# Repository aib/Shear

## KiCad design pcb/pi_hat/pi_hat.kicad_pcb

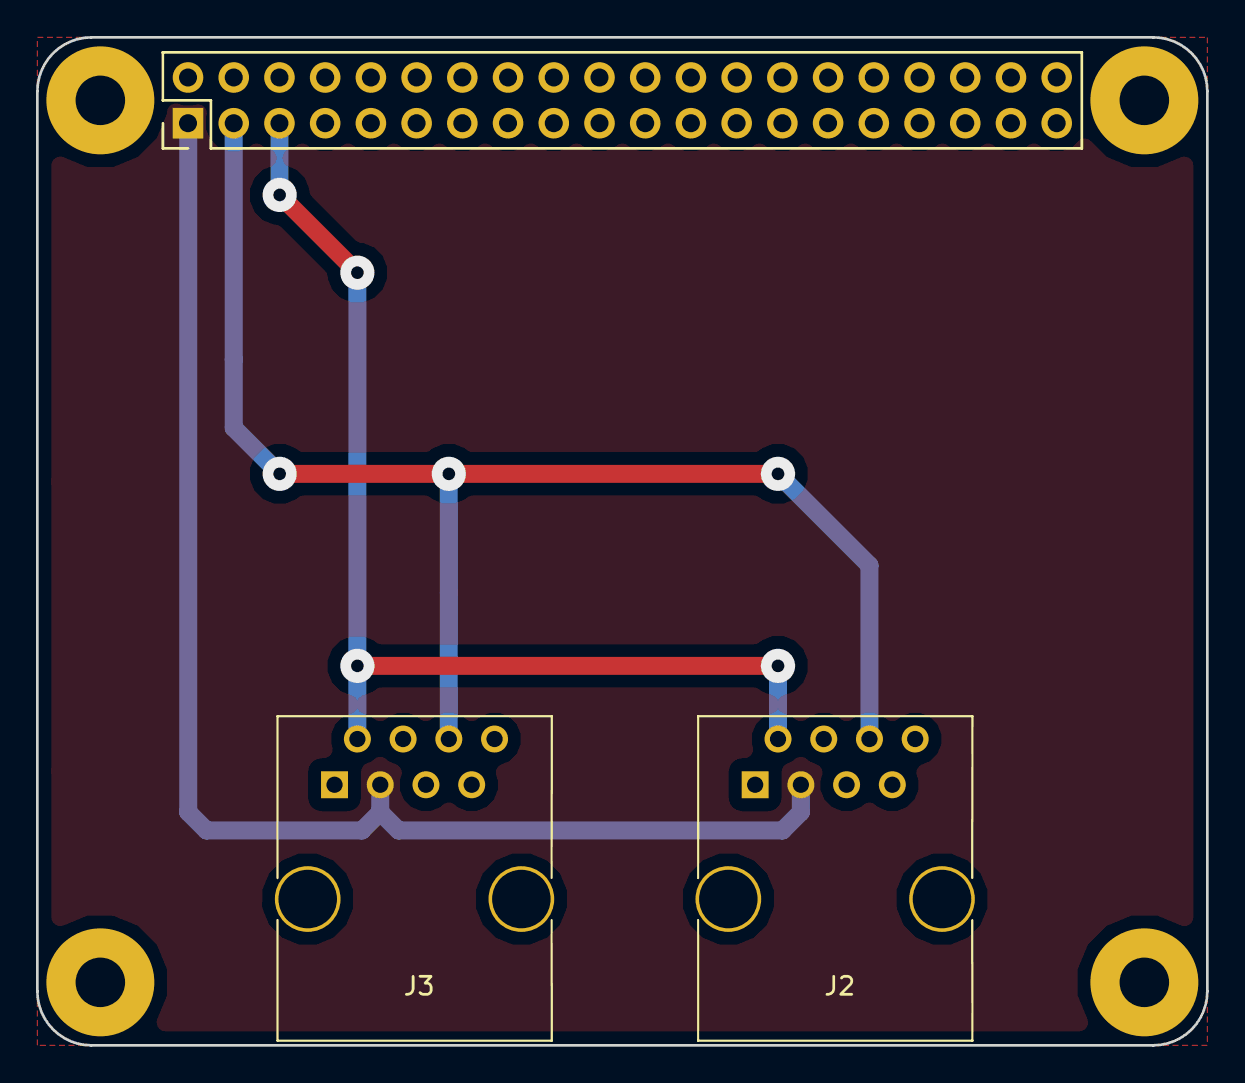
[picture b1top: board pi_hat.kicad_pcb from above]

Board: 2 copper layers, 65.0 x 56.0 mm, 3 parts (0 on the bottom side), 4 nets.

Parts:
J1: Conn_02x20_Odd_Even; RaspberryPi_3_ModelB
J2, J3: RJ45; RJ45_8

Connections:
/SCL: J1.5, J2.2, J3.2
/SDA: J1.3, J2.6, J3.6
GND: J1.9, J2.1, J3.1
VCC: J1.1, J2.3, J3.3

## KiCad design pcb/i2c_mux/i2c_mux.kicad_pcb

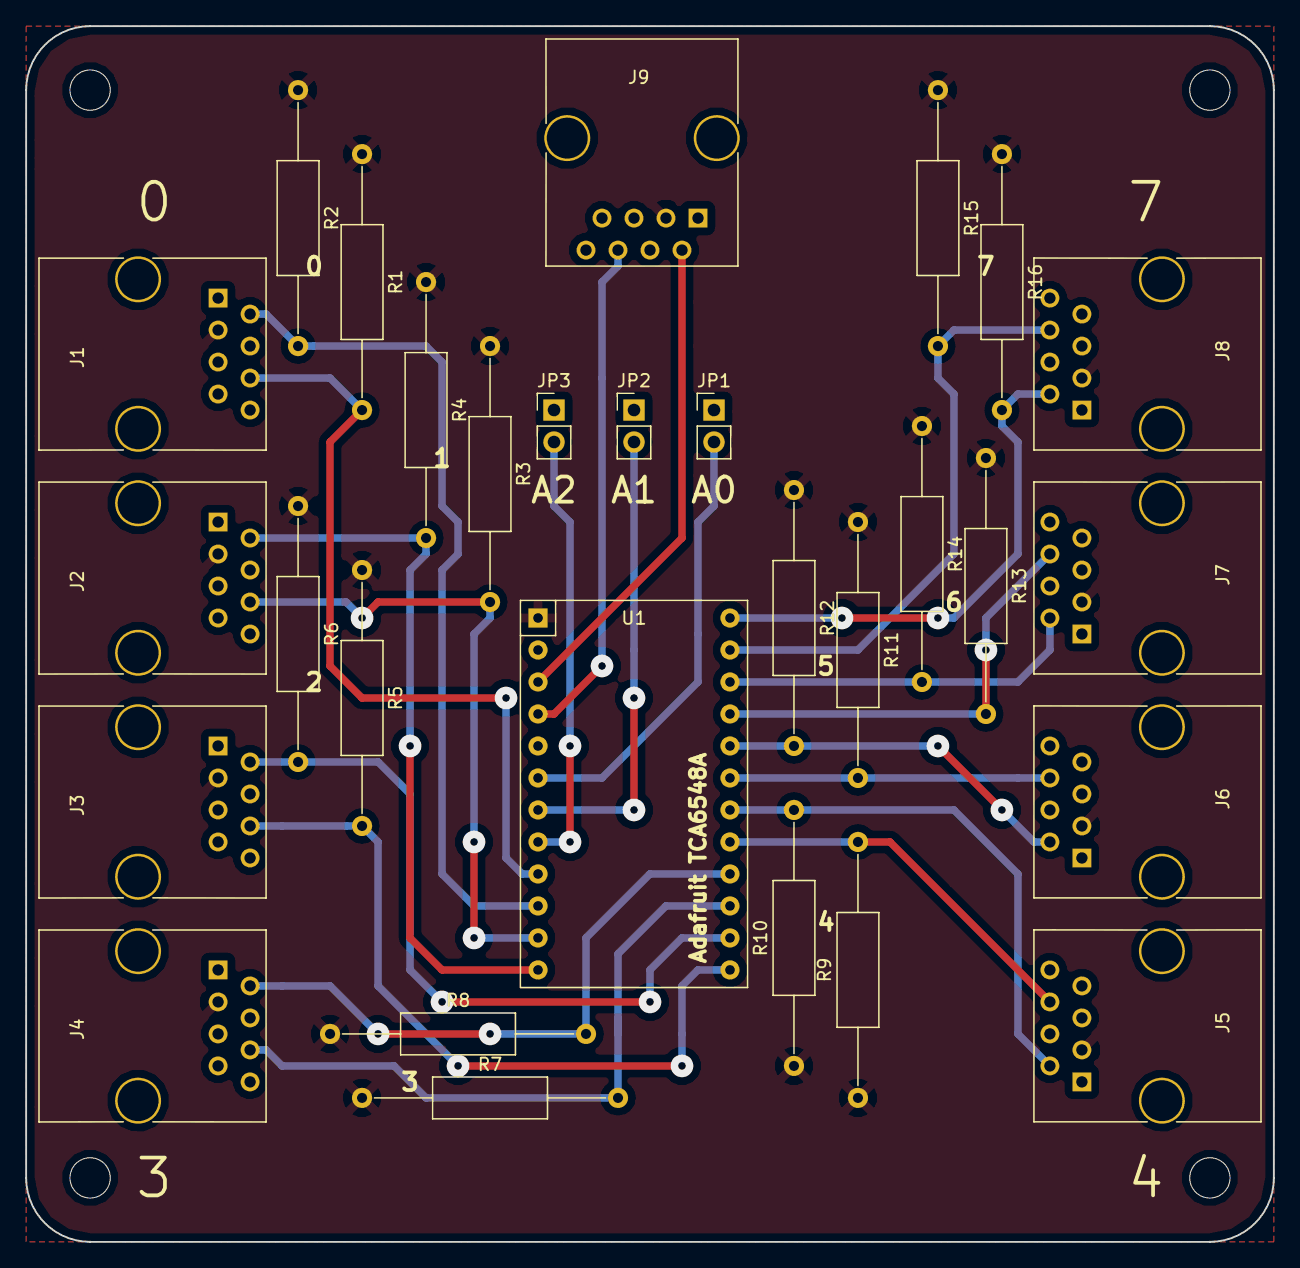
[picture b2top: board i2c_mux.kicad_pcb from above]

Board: 2 copper layers, 99.1 x 96.5 mm, 29 parts (0 on the bottom side), 23 nets.

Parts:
J1, J2, J3, J4, J5, J6, J7, J8, J9: RJ45; RJ45_8
JP1, JP2, JP3: Jumper_NO_Small; Pin_Header_Straight_1x02_Pitch2.54mm
R1, R2, R3, R4, R5, R6, R7, R8, R9, R10, R11, R12, R13, R14, R15, R16: R_Small; R_Axial_DIN0309_L9.0mm_D3.2mm_P20.32mm_Horizontal
U1: Adafruit_TCA6548A; Adafruit_TCA9548A

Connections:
GND: J1.1, J2.1, J3.1, J4.1, J5.1, J6.1, J7.1, J8.1, J9.1, JP1.1, JP2.1, JP3.1, U1.2
unnamed: J1.2, R2.2, U1.10
unnamed: J1.6, R1.2, U1.9
unnamed: J2.2, R4.2, U1.12
unnamed: J2.6, R3.2, U1.11
unnamed: J3.2, R6.2, U1.14
unnamed: J3.6, R5.2, U1.13
unnamed: J4.2, R8.2, U1.16
unnamed: J4.6, R7.2, U1.15
unnamed: J5.2, R10.2, U1.18
unnamed: J5.6, R9.2, U1.17
unnamed: J6.2, R12.2, U1.20
unnamed: J6.6, R11.2, U1.19
unnamed: J7.2, R14.2, U1.22
unnamed: J7.6, R13.2, U1.21
unnamed: J8.2, R16.2, U1.24
unnamed: J8.6, R15.2, U1.23
unnamed: J9.2, U1.3
unnamed: J9.6, U1.4
unnamed: JP1.2, U1.6
unnamed: JP2.2, U1.7
unnamed: JP3.2, U1.8
VCC: J1.3, J2.3, J3.3, J4.3, J5.3, J6.3, J7.3, J8.3, J9.3, R1.1, R2.1, R3.1, R4.1, R5.1, R6.1, R7.1, R8.1, R9.1, R10.1, R11.1, R12.1, R13.1, R14.1, R15.1, R16.1, U1.1

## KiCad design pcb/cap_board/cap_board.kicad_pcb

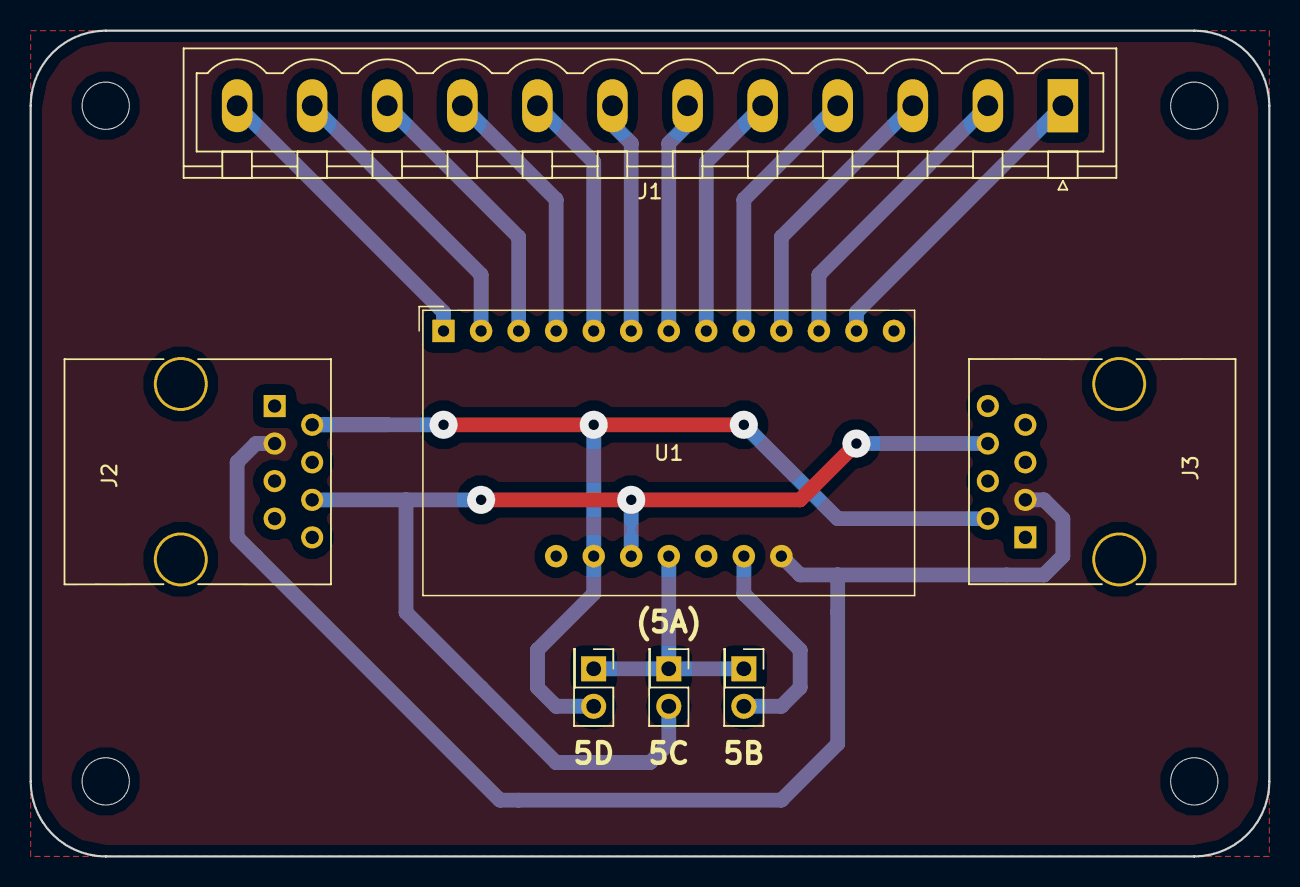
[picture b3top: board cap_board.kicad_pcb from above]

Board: 2 copper layers, 83.8 x 55.9 mm, 7 parts (0 on the bottom side), 18 nets.

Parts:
J1: Conn_01x12; PhoenixContact_MSTBVA-G_12x5.08mm_Vertical
J2, J3: RJ45; RJ45_8
JP1, JP2, JP3: Jumper_NO_Small; Pin_Header_Straight_2x01_Pitch2.54mm
U1: Adafruit_MPR121

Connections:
/SCL: J2.2, J3.2, JP3.2, U1.2
/SDA: J2.6, J3.6, JP2.2, U1.3
GND: J2.1, J3.1, U1.5, U1.8
unnamed: J1.1, U1.9
unnamed: J1.2, U1.10
unnamed: J1.3, U1.11
unnamed: J1.4, U1.12
unnamed: J1.5, U1.13
unnamed: J1.6, U1.14
unnamed: J1.7, U1.15
unnamed: J1.8, U1.16
unnamed: J1.9, U1.17
unnamed: J1.10, U1.18
unnamed: J1.11, U1.19
unnamed: J1.12, U1.20
unnamed: JP1.1, JP2.1, JP3.1, U1.4
unnamed: JP1.2, U1.6
VCC: J2.3, J3.3, U1.7

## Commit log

2016-09-20 Add link to Raspbian distribution
2016-09-20 Add ansible config with sensible defaults
2016-09-20 Add tool for detecting MPR121's on the I2C bus
2016-09-20 Add Ansible script setting up the Pi
    ...with only I2C stuff for now
2016-09-20 Use rsync to copy project directory to Pi
2016-09-20 Import Adafruit's MPR121 library
2016-09-20 Import Adafruit's GPIO library
2016-09-20 Ignore Python cache files
2018-11-19 Add 'sudo' to an external command requiring root
2018-11-19 Install Python 3 and pip
2018-11-19 Group apt installs
2018-11-19 Change MPR121 settings to match those of Bare Conductive
2018-11-19 Ignore /misc/
2018-11-19 Add fluidsynth, a SF2 and audio libraries
2018-11-19 Install Adafruit's PureIO library
2018-11-19 Remove pi-bluetooth and ntp
2018-11-19 Add script for testing the modules
2018-11-19 Remove packages no longer needed
2018-11-19 Disable some unnecessary boot scripts
2018-11-19 Add midi.py written earlier
2018-11-19 Add prototype instrument program
    with MIDI output and key mapping
2018-11-19 Add error handling; shields can now be hot plugged
2018-11-19 Enable all shields
2018-11-19 Add runner script for Fluidsynth
2018-11-19 Mount filesystems read-only
2018-11-19 Send all notes off on Ctrl-C
2018-11-19 Use insserv instead of the service module to disable services
    Do not disable console-setup
2018-11-19 Remove instrument.py
2018-11-19 Do not install i2c-tools twice!
2018-11-19 Remove unnecessary packages, use busybox syslogd instead of rsyslog
2018-11-19 Rename "become"s to "sudo"s; deprecation be damned!
2018-11-19 Run synth and keyboard at boot
2018-11-19 Increase DHCP lease time to 4h
2018-11-19 Set fluidsynth gain
2018-11-19 Install python-rtmidi
2018-11-19 Load SF2 in cfg file and set channels
2018-11-19 Start tuning the instrument
2018-11-19 Change to a dual-setup midi.py
2018-11-19 Filter *.pyc while copying
2018-11-19 Add scripts for setting up an ethernet connection with the Pi
2018-11-19 Do not use a lease file for the DHCP server
2018-11-19 Change kernel parameters
2018-11-19 Set sound output and value
2018-11-19 Rename runfluid.sh to run.sh
2018-11-19 Print MIDI notes (and channel) along with key numbers
2018-11-19 Add the MPR121 breakout footprint
2018-11-19 Add ansible inventory file
2018-11-19 Disable keyboard-setup and console-setup
2018-11-19 Add the MPR121 breakout schematic component
2018-11-19 Add the Pi hat project
2018-11-19 Add the TT setup
2018-11-19 Remove 'misc' directory, most of the stuff is already in my dotfiles
2018-11-19 Revert "Add the TT setup"
    This reverts commit 7f819ac6f6b5824fb270671cab77ea756a12f661.
2018-11-19 Add private key file since ansible now seems to accept relative paths
2018-11-19 Add the initial PCB design
2018-11-19 Add front plate zone
2018-11-19 Change screw terminals to 5.08mm pitch and add RJ45 footprints
2018-11-19 Add mounting holes and round the board
2018-11-19 Revert "Change to a dual-setup midi.py"
    This reverts commit 23491e4e4b4dfb68b9938927f0bcc5239a5617bc.
2018-11-19 Add the sensor board project
2018-11-19 Trade the long ground loop for a 5th jumper :/
2018-11-19 Change +5V to VCC
2018-11-19 Move cap_board's .gitignore to pcb
2018-11-19 Remove superfluous option -o StrichHostKeyChecking=no
2018-11-19 Add empty I2C multiplexer project
2018-11-19 Add a board design with 4 jumpers and a long ground return :/
2018-11-19 Also ignore *.bck
2018-11-19 Add a base Raspberry Pi 3 footprint
2018-11-19 Ignore backup and generated files
2018-11-19 Use 3.3V and assign footprints
2018-11-19 Ignore ansible/*.retry
2018-11-19 Add new design with fewer jumpers and the RJ45 connectors on a side
2018-11-19 Do not ignore /misc/ -- it does not exist
2018-11-19 Use the ground on pin 9
2018-11-19 Use a 12-pin connector and add silkscreen text
2018-11-19 Add the multiplexer board without pull-ups
2018-11-19 Add I2C multiplexer board v1.00
2018-11-19 Add bus switch support to main code
2018-11-19 Pass MIDI port to key_change, d'oh
2018-11-19 Add a preliminary fluidsynth config for v2
2018-11-19 Add MPR121 wrapper with bus switching support
2018-11-19 Shorten the multiplexer board to fit 100mm x 100mm
2018-11-19 Add component assignments
2018-11-19 Add bus switching support to captest
2018-11-19 Add a preliminary cap board config for v2
2018-11-19 Center the central components (mux v1.02)
2018-11-19 Fix SDA/SCL mix-up and pull RST up
2018-11-19 Use a constant for the MIDI port/pid regex
2018-11-19 Pull address selectors up instead of down and move a via
2018-11-19 Add pull-up resistors to the I2C multiplexer board
2018-11-19 Use a key_change function
2018-11-19 Add signature and version marker to the Pi hat
2018-11-19 Fix silence only silencing the first channel
2018-11-19 Add support for custom/callable keys
2018-11-19 Tune the instrument for v3
2018-11-19 Add instrument switching key handlers
2018-11-19 Add the instruments and the special keys
2018-11-19 Fix the silence on exit
2018-11-19 Change instrument mapping (version GGWP)
2018-11-19 Use multiplexer ports 0 and 1 (for the new mux hat)
2018-11-19 Add helper function midi_silence_all
2018-11-19 Add v2 first mapping
2018-11-19 Remove the pi_hat and i2c_mux projects as the new pi_i2c_mux_hat should cover both
2018-11-19 Remove the channel initialization and change the font in fluidsynth.cfg
2018-11-19 Initialize the channel/instrument map on connect
2018-11-19 Add midi_channel_instrument_change function taking an instrument index lambda
2018-11-19 Rename insts to channel_map
2018-11-19 Add helper function midi_change_instrument
2018-11-19 Add the new synth configuration
2018-11-19 Remove old captest code
2018-11-19 Remove the old special key functions
2018-11-19 Detect and print when the MIDI connection status changes
2018-11-19 Add default channel 4
2019-12-08 Change note assignment: lower the main portion, smooth out some peaks
